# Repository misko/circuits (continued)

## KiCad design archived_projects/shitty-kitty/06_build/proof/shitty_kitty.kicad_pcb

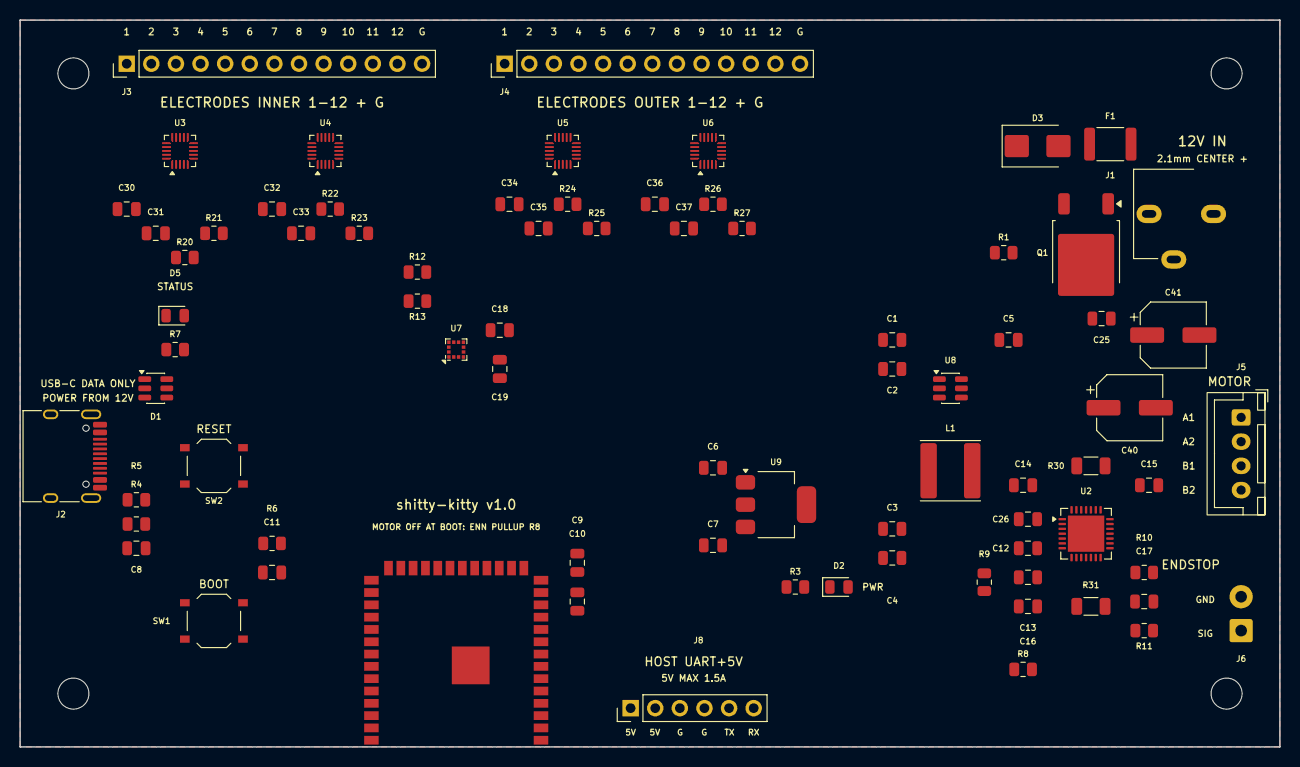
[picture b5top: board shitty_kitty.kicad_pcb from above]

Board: 4 copper layers, 130.0 x 75.0 mm, 82 parts (0 on the bottom side), 79 nets, no tracks yet.

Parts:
C1, C2: 4.7u buck in; C_0805_2012Metric
C3, C4: 22u buck out; C_0805_2012Metric
C5: 100n BST; C_0805_2012Metric
C6: 4.7u LDO in; C_0805_2012Metric
C7: 22u LDO out; C_0805_2012Metric
C8: 100n VBUS; C_0805_2012Metric
C9: 22u MCU 3V3; C_0805_2012Metric
C10: 100n MCU 3V3; C_0805_2012Metric
C11: 1u EN; C_0805_2012Metric
C12: 100n VCP; C_0805_2012Metric
C13: 4.7u 5VOUT; C_0805_2012Metric
C14, C15: 100n VS; C_0805_2012Metric
C16: 100n VCC_IO; C_0805_2012Metric
C17: 100n endstop; C_0805_2012Metric
C18: 100n accel; C_0805_2012Metric
C19: 22u accel; C_0805_2012Metric
C25: 100n 12V; C_0805_2012Metric
C26: 22n CP fly; C_0805_2012Metric
C30, C32, C34, C36: 100n MPR VDD; C_0805_2012Metric
C31, C33, C35, C37: 100n VREG; C_0805_2012Metric
C40: 100u 12V bulk; CP_Elec_6.3x7.7
C41: 100u VS bulk; CP_Elec_6.3x7.7
D1: USBLC6-2SC6; SOT-23-6
D2: green PWR; LED_0805_2012Metric
D3: SMBJ16A; D_SMB
D5: green STATUS; LED_0805_2012Metric
F1: 2A polyfuse 16V; Fuse_1812_4532Metric
H1, H2, H3, H4: MountingHole_3.2mm_M3
J1: DC-005C-20A 12V; DCJack_DC005_Horizontal
J2: TYPE-C-31-M-12; USB_C_Receptacle_HRO_TYPE-C-31-M-12
J3: ELECTRODES INNER; PinHeader_1x13_P2.54mm_Vertical
J4: ELECTRODES OUTER; PinHeader_1x13_P2.54mm_Vertical
J5: MOTOR NEMA17; JST_XH_B4B-XH-A_1x04_P2.50mm_Vertical
J6: ENDSTOP TERM; TerminalBlock_3.5-2P_NoSilk
J8: HOST 1x6; PinHeader_1x06_P2.54mm_Vertical
L1: 10uH SWPA6045S; L_Sunlord_SWPA6045S
Q1: AOD4185 revpol; TO-252-2
R1: 100k gate pd; R_0805_2012Metric
R3: 1k LED; R_0805_2012Metric
R4: 5.1k CC1; R_0805_2012Metric
R5: 5.1k CC2; R_0805_2012Metric
R6: 10k EN; R_0805_2012Metric
R7: 1k status LED; R_0805_2012Metric
R8: 10k ENN pu; R_0805_2012Metric
R9: 1k TMC UART; R_0805_2012Metric
R10: 10k endstop pu; R_0805_2012Metric
R11: 1k endstop ser; R_0805_2012Metric
R12: 4.7k SDA pu; R_0805_2012Metric
R13: 4.7k SCL pu; R_0805_2012Metric
R20, R22, R24, R26: 75k REXT; R_0805_2012Metric
R21, R23, R25, R27: 10k IRQ pu; R_0805_2012Metric
R30: 0.15R sense A; R_1206_3216Metric
R31: 0.15R sense B; R_1206_3216Metric
SW1: TS-1187A BOOT; SW_Push_1P1T_XKB_TS-1187A
SW2: TS-1187A RESET; SW_Push_1P1T_XKB_TS-1187A
U1: ESP32-S3-WROOM-1-N8R2; ESP32-S3-WROOM-1
U2: TMC2209-LA-T; QFN-28-1EP_5x5mm_P0.5mm_EP3.75x3.75mm
U3: MPR121QR2 0x5A; UQFN-20_3x3mm_P0.4mm
U4: MPR121QR2 0x5B; UQFN-20_3x3mm_P0.4mm
U5: MPR121QR2 0x5C; UQFN-20_3x3mm_P0.4mm
U6: MPR121QR2 0x5D; UQFN-20_3x3mm_P0.4mm
U7: LIS2DH12TR; LGA-12_2x2mm_P0.5mm
U8: AP63205WU-7; TSOT-23-6
U9: AMS1117-3.3; SOT-223-3_TabPin2

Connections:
3V3: C7.1, C9.1, C10.1, C16.1, C18.1, C19.1, C30.1, C32.1, C34.1, C36.1, R3.1, R6.1, R8.1, R10.1, R12.1, R13.1, R21.1, R23.1, R25.1, R27.1, U1.2, U2.15, U3.20, U4.4, U4.20, U5.20, U6.20, U7.2, U7.9, U7.10, U9.2
5V: C3.1, C4.1, C6.1, J8.1, J8.2, L1.2, U8.1, U9.3
ACC_INT: U1.20, U7.12
BOOT: SW1.1, U1.27
BRA: R30.1, U2.23
BRB: R31.1, U2.27
BST: C5.1, U8.6
CC1: J2.A5, R4.1
CC2: J2.B5, R5.1
CPI: C26.2, U2.5
CPO: C26.1, U2.4
DIAG: U1.7, U2.11
DIR: U1.5, U2.19
EN: C11.1, R6.2, SW2.1, U1.3
ENDSTOP_G: R11.2, U1.9
ENDSTOP_N: C17.1, J6.1, R10.2, R11.1
ENN: R8.2, U1.6, U2.2
GATE_Q1: Q1.1, R1.1
GND: C1.2, C2.2, C3.2, C4.2, C6.2, C7.2, C8.2, C9.2, C10.2, C11.2, C13.2, C14.2, C15.2, C16.2, C17.2, C18.2, C19.2, C25.2, C30.2, C31.2, C32.2, C33.2, C34.2, C35.2, C36.2, C37.2, C40.2, C41.2, D1.2, D2.1, D3.2, D5.1, J1.2, J1.3, J2.A1, J2.A12, J2.B1, J2.B12, J2.SH, J3.13, J4.13, J6.2, J8.3, J8.4, R1.2, R4.2, R5.2, R20.2, R22.2, R24.2, R26.2, R30.2, R31.2, SW1.2, SW2.2, U1.1, U1.40, U1.41, U2.3, U2.7, U2.9, U2.10, U2.13, U2.18, U2.29, U3.4, U3.6, U4.6, U5.6, U6.6, U7.3, U7.5, U7.6, U7.7, U7.8, U8.4, U9.1
HOST_RX: J8.6, U1.36
HOST_TX: J8.5, U1.37
INDEX: U1.8, U2.12
INNER1: J3.1, U3.8
INNER2: J3.2, U3.9
INNER3: J3.3, U3.10
INNER4: J3.4, U3.11
INNER5: J3.5, U3.12
INNER6: J3.6, U3.13
INNER7: J3.7, U4.8
INNER8: J3.8, U4.9
INNER9: J3.9, U4.10
INNER10: J3.10, U4.11
INNER11: J3.11, U4.12
INNER12: J3.12, U4.13
LED_A: D2.2, R3.2
LED_SA: D5.2, R7.2
LED_ST: R7.1, U1.21
MOT_A1: J5.1, U2.24
MOT_A2: J5.2, U2.21
MOT_B1: J5.3, U2.26
MOT_B2: J5.4, U2.1
MPR_IRQ1: R21.2, U1.12, U3.1
MPR_IRQ2: R23.2, U1.17, U4.1
MPR_IRQ3: R25.2, U1.18, U5.1
MPR_IRQ4: R27.2, U1.19, U6.1
OUTER1: J4.1, U5.8
OUTER2: J4.2, U5.9
OUTER3: J4.3, U5.10
OUTER4: J4.4, U5.11
OUTER5: J4.5, U5.12
OUTER6: J4.6, U5.13
OUTER7: J4.7, U6.8
OUTER8: J4.8, U6.9
OUTER9: J4.9, U6.10
OUTER10: J4.10, U6.11
OUTER11: J4.11, U6.12
OUTER12: J4.12, U6.13
REXT_U3: R20.1, U3.7
REXT_U4: R22.1, U4.7
REXT_U5: R24.1, U5.7
REXT_U6: R26.1, U6.7
SCL: R13.2, U1.38, U3.2, U4.2, U5.2, U6.2, U6.4, U7.1
SDA: R12.2, U1.39, U3.3, U4.3, U5.3, U5.4, U6.3, U7.4
STEP: U1.4, U2.16
SW_BUCK: C5.2, L1.1, U8.5
TMC_TX: R9.1, U1.10
TMC_UART: R9.2, U1.11, U2.14
USB_DM: D1.3, D1.4, J2.A7, J2.B7, U1.13
USB_DP: D1.1, D1.6, J2.A6, J2.B6, U1.14
USB_VBUS: C8.1, D1.5, J2.A4, J2.A9, J2.B4, J2.B9
V5OUT: C13.1, U2.8
VCP: C12.1, U2.6
VIN_12V: C1.1, C2.1, C12.2, C14.1, C15.1, C25.1, C40.1, C41.1, D3.1, Q1.3, U2.22, U2.28, U8.2, U8.3
VIN_F: F1.2, Q1.2
VIN_RAW: F1.1, J1.1
VREG_U3: C31.1, U3.5
VREG_U4: C33.1, U4.5
VREG_U5: C35.1, U5.5
VREG_U6: C37.1, U6.5
